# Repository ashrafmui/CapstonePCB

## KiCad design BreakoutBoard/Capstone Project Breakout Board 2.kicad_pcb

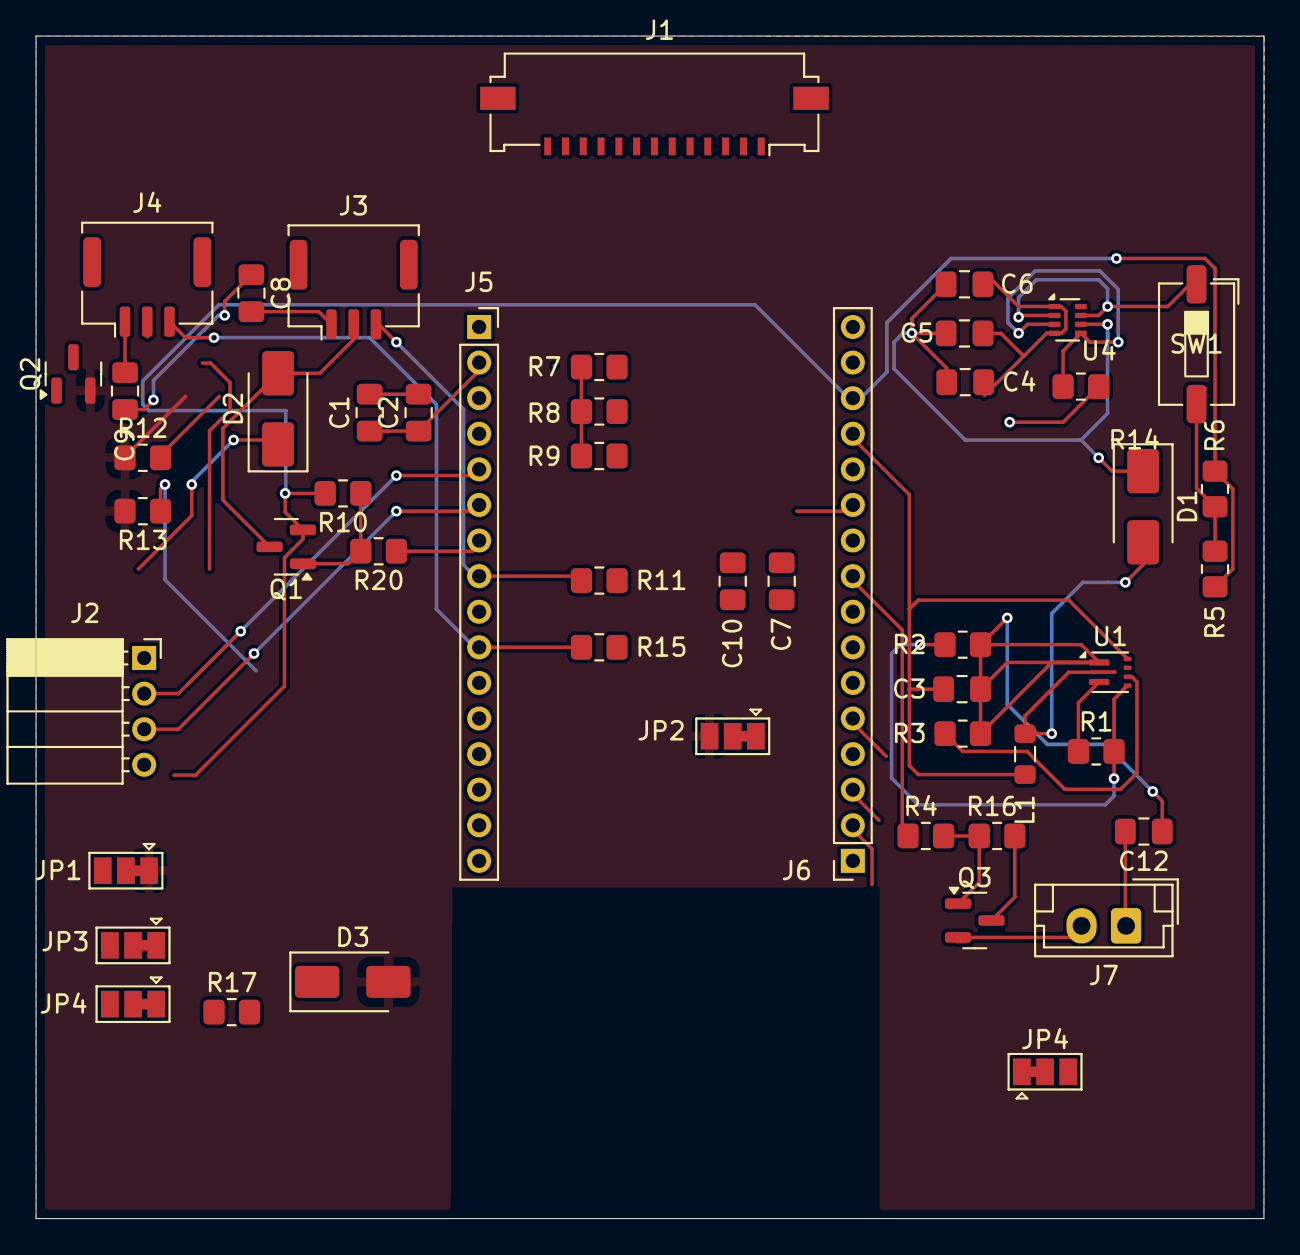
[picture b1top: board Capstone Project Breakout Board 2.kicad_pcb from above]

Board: 2 copper layers, 69.0 x 66.4 mm, 51 parts (0 on the bottom side), 40 nets.

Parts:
C1, C10: 47 uF; C_0805_2012Metric_Pad1.18x1.45mm_HandSolder
C2, C7: 0.1 uF; C_0805_2012Metric_Pad1.18x1.45mm_HandSolder
C3, C4, C5, C6: 22 uF; C_0805_2012Metric_Pad1.18x1.45mm_HandSolder
C8, C9, C12: 47uF; C_0805_2012Metric_Pad1.18x1.45mm_HandSolder
D1, D2, D3: SS14; D_SMA
J1: Conn_01x15; Molex_200528-0130_1x13-1MP_P1.00mm_Horizontal
J2: Conn_01x04; PinSocket_1x04_P2.00mm_Horizontal
J3, J4: Conn_01x03_MountingPin; Molex_CLIK-Mate_502382-0370_1x03-1MP_P1.25mm_Vertical
J5, J6: Conn_01x16; PinSocket_1x16_P2.00mm_Vertical
J7: Conn_01x02; JST_EH_B2B-EH-A_1x02_P2.50mm_Vertical
JP1: Jumper3; SolderJumper-3_P1.3mm_Bridged12_Pad1.0x1.5mm
JP2, JP3, JP4, JP4#2: SolderJumper_3_Bridged12; SolderJumper-3_P1.3mm_Bridged12_Pad1.0x1.5mm
L1: 1 uH; L_0805_2012Metric_Pad1.05x1.20mm_HandSolder
Q1, Q2, Q3: AO3400A; SOT-23
R1: 732k; R_0805_2012Metric_Pad1.20x1.40mm_HandSolder
R2, R3, R10, R12, R14: 100k; R_0805_2012Metric_Pad1.20x1.40mm_HandSolder
R4, R13, R20: 100; R_0805_2012Metric_Pad1.20x1.40mm_HandSolder
R5: 0; R_0805_2012Metric_Pad1.20x1.40mm_HandSolder
R6, R7, R8, R9, R11, R15, R17: 10k; R_0805_2012Metric_Pad1.20x1.40mm_HandSolder
R16: 1M; R_0805_2012Metric_Pad1.20x1.40mm_HandSolder
SW1: SW_Push; SW_DIP_SPSTx01_Slide_6.7x4.1mm_W6.73mm_P2.54mm_LowProfile_J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
U1: TPS61022; Texas_RWU0007A_VQFN-7_2x2mm_P0.5mm
U4: TPS2116DRL; SOT-583-8

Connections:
3.3V: C1.2, C2.2
5U: C7.2, C10.2
+3.3V: J1.1, J1.3, J1.8, J1.10, R7.1, R8.1, R9.1, R11.2, R15.2, R17.1
+5C: C4.1, C5.1, C6.1, C8.1, C9.1, D1.1 (K), D2.1 (K), D3.1 (K), U4.6 (VIN2)
+5U: R14.2, U4.3 (VIN1), U4.5 (MODE)
+5V: C3.1, C4.2, C5.2, C6.2, C12.1, J1.2, J1.9, J2.4, J6.14, JP1.3 (B), JP3.3 (B), JP4.3 (B), Q1.2 (S), Q3.3 (D), R2.2, R3.2, R5.1, R6.2, R10.2, R12.2, R14.1, R16.2, U1.1 (GND), U4.1 (GND), U4.4 (PR1)
/PS: J1.7, JP4.2 (C)
/SPEAKER +: C12.2, J7.1
/SPEAKER -: J7.2, Q3.2 (S)
A0: J2.2, J5.5
AB0: J1.11, J6.3, JP2.2 (C)
AB1: J1.4, J6.4, JP3.2 (C)
D0: J2.3, J5.6
Fan1: J5.7, R20.1
Fan2: J5.9, R13.1
GND: D3.2 (A), JP1.1 (A), JP2.3 (B), Q2.2 (S), R12.1, R13.2
GPIO34: J3.3, J5.8, R11.1
GPIO35: J4.3, J5.10, R15.1
IRQ: J1.12, J6.5
unnamed: D1.2 (A), L1.2, U1.2 (SW)
unnamed: D2.2 (A), J3.2, Q1.3 (D)
unnamed: J4.2, Q2.3 (D)
unnamed: C8.2, J3.1
unnamed: C9.2, J4.1
unnamed: C1.1, C2.1, J5.2
unnamed: C7.1, C10.1, J6.11
unnamed: C3.2, J6.13, L1.1, U1.7 (VIN)
unnamed: JP2.1 (A), R7.2
unnamed: JP3.1 (A), R8.2
unnamed: JP4.1 (A), R17.2
unnamed: Q1.1 (G), R10.1, R20.2
unnamed: Q3.1 (G), R4.2, R16.1
unnamed: R5.2, R6.1, SW1.2
unnamed: SW1.1, U4.2 (VOUT), U4.7 (VOUT)
unnamed: R3.1, U1.5 (EN)
unnamed: R1.2, R2.1, U1.4 (FB)
unnamed: R1.1, U1.3 (VOUT)
SCL: J1.6, J6.2
SDA: J1.5, J6.1
SPEAKER: J6.9, R4.1

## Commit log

2025-11-03 pcb file
2025-11-03 removed redundant files
